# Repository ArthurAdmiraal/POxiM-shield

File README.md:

# POxiM-shield
 Prototyping Arduino shield for POxiM Pulse/Oxymeter

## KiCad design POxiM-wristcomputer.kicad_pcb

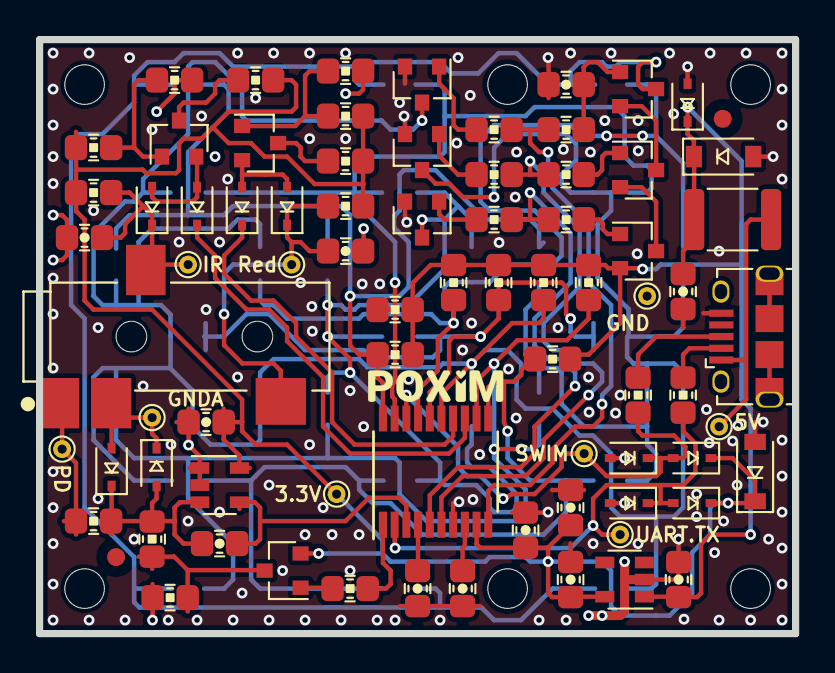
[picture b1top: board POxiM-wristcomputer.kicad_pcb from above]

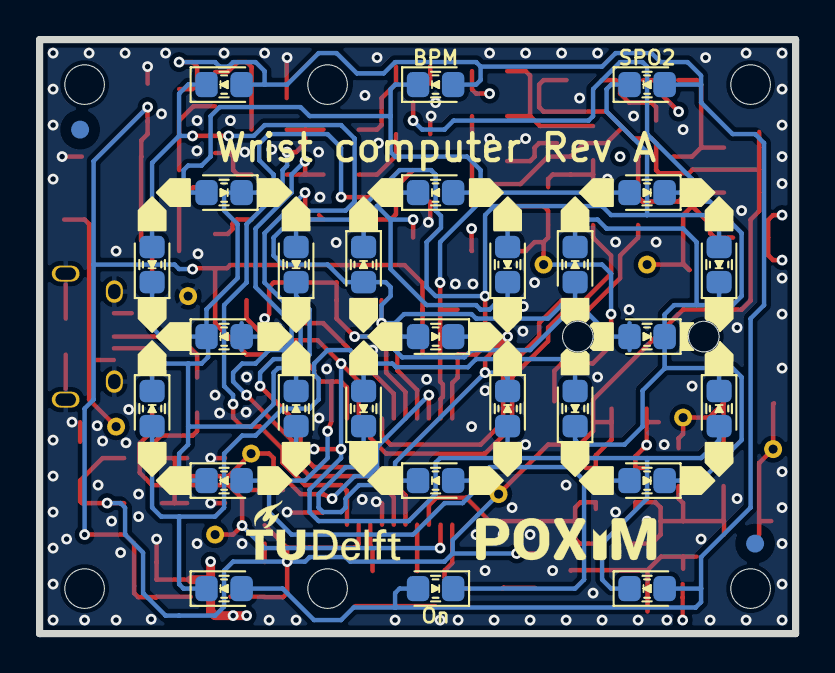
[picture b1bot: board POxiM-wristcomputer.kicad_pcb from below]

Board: 4 copper layers, 42.0 x 33.0 mm, 115 parts (35 on the bottom side), 50 nets.

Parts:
C1, C3, C7, C9, C11: 100nF; C_0805_2012Metric_0603_1608Metric
C2: 39pF; C_0805_2012Metric_0603_1608Metric
C4, C5, C6, C8, C12: 2.2µF; C_0805_2012Metric_0603_1608Metric
C10: 470nF; C_0805_2012Metric_0603_1608Metric
D1, D2, D3, D4, D5, D6, D35, D36, D37, D38, D39: Schottky; D_SOD-323
D7, D8, D9, D10, D11, D12, D13, D14, D15, D16, D17, D18, D19, D20, D21, D22, D23, D24, D25, D26, D27, D28, D29, D30, D31, D32, D33: LED; LED_0805_2012Metric_0603_1608Metric
D34: 6.8V; D_SOD-123
D40: 5.6V; D_SOD-123
F1: 500mA; R_1812_4532Metric
FID1, FID2, FID3, FID4: Fiducial; Fiducial_1mm_Mask2mm
H1, H2, H3, H4: MountingHole; MountingHole_2.2mm_M2
H5, H6: AlignmentHole; AlignmentHole_2.2mm_M2
J1: Power in; USB_Micro-B_Amphenol_10103594-0001LF_Horizontal
J2: To finger probe; CUI_SJ-43514-SMT
JP1: SWIM jumper; R_0805_2012Metric_0603_1608Metric
JP2: UART out jumper; R_0805_2012Metric_0603_1608Metric
NT1, NT2: Net-Tie_2; NetTie-2_SMD_Pad0.5mm
Q1, Q2, Q3: MMBT3904,215; SOT-23
Q4, Q5, Q6, Q7, Q8, Q9: PMBT3906,215; SOT-23
R1: 4.7MΩ; R_0805_2012Metric_0603_1608Metric
R2, R24, R25: 33kΩ; R_0805_2012Metric_0603_1608Metric
R3, R4: 100kΩ; R_0805_2012Metric_0603_1608Metric
R5, R6, R7, R8, R9, R10, R12: 560Ω; R_0805_2012Metric_0603_1608Metric
R11, R20: 2.2kΩ; R_0805_2012Metric_0603_1608Metric
R13, R14, R15, R16, R17, R18, R19, R21: 3.3kΩ; R_0805_2012Metric_0603_1608Metric
R22, R23: 68Ω; R_0805_2012Metric_0603_1608Metric
TP1: 5V in; TestPoint_THTPad_D1.0mm_Drill0.5mm
TP2: SWIM; TestPoint_THTPad_D1.0mm_Drill0.5mm
TP3: UART.TX; TestPoint_THTPad_D1.0mm_Drill0.5mm
TP4: GND; TestPoint_THTPad_D1.0mm_Drill0.5mm
TP5: PhotoDiode; TestPoint_THTPad_D1.0mm_Drill0.5mm
TP6: LED.Red; TestPoint_THTPad_D1.0mm_Drill0.5mm
TP7: GNDA; TestPoint_THTPad_D1.0mm_Drill0.5mm
TP8: LED.IR; TestPoint_THTPad_D1.0mm_Drill0.5mm
TP9: 3.3V; TestPoint_THTPad_D1.0mm_Drill0.5mm
U1: LM321; SOT-23-5
U2: STM8S003F3P; TSSOP-20_4.4x6.5mm_P0.65mm
U3: MIC5504-3.3YM5; SOT-23-5

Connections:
+3V3: C1.1, C5.1, C8.1, C9.1, D36.1, D38.1, D40.1, Q7.2, R11.2, R20.2, R22.2, R23.2, R24.2, R25.2, TP9.1, U1.5, U2.9, U3.5
+5V: C4.1, C11.1, D34.1, D35.1, F1.1, Q4.2, R5.1, R6.1, R7.1, R8.1, R9.1, R10.1, R12.1, U3.1
/Display/Common0: R14.2, R18.2, U2.6
/Display/Common1: R16.2, R17.2, U2.5
/Display/Common2: R15.2, R19.2, U2.10
/Display/Segment0: D7.2, D14.2, D21.1, D22.2, R12.2, U2.19
/Display/Segment1: D8.2, D15.2, D23.1, D24.2, R5.2, U2.17
/Display/Segment2: D9.2, D16.2, D25.1, D26.2, R6.2, U2.20
/Display/Segment3: D10.2, D17.2, D28.2, R7.2, U2.16
/Display/Segment4: D11.2, D18.2, D29.1, D30.2, R8.2, U2.15
/Display/Segment5: D12.2, D19.2, D31.1, D32.2, R9.2, U2.12
/Display/Segment6: D13.2, D20.2, D27.1, D33.2, R10.2, U2.11
/Microcontroller/ADC.feedback: R3.1, U2.1
/Microcontroller/ADC.input: C2.1, U1.4, U2.3
/Microcontroller/LED.IR: D2.1, U2.13
/Microcontroller/LED.Red: D1.1, U2.14
/Microcontroller/NRST: C7.1, U2.4
/Microcontroller/SWIM: D36.2, D37.1, JP1.2, TP2.1, U2.18
/Microcontroller/VCAP: C10.1, U2.8
/Signal conditioning/LEDOut.IR: C12.1, D4.1, J2.R1, R25.1, TP8.1
/Signal conditioning/LEDOut.Red: C6.1, D3.1, J2.T, R24.1, TP6.1
/Signal conditioning/PhotoDiode: J2.S, R2.2, TP5.1
/Signal conditioning/PhotoDiodeInternal: C2.2, D5.2, D6.1, R1.1, R2.1, U1.3
/USB interface/5V_input: F1.2, J1.1, TP1.1
/USB interface/Data+: J1.3, JP1.1
/USB interface/Data-: J1.2, JP2.1
/USB interface/DataTX: D38.2, D39.1, JP2.2, TP3.1, U2.2
GND: C3.2, C4.2, C5.2, C7.2, C8.2, C9.2, C10.2, C11.2, D34.2, D35.2, D37.2, D39.2, D40.2, J1.5, J1.6, NT1.1, NT2.1, Q1.2, Q2.2, Q3.2, TP4.1, U2.7, U3.2
GNDA: C6.2, C12.2, D5.1, D6.2, J2.R2, NT2.2, R13.1, R21.1, TP7.1
GNDREF: C1.2, NT1.2, R4.2, U1.1, U1.2
unnamed: C3.1, Q6.1, R19.1
unnamed: D1.2, D3.2, Q8.2
unnamed: D2.2, D4.2, Q9.2
unnamed: D7.1, D8.1, D9.1, D10.1, D11.1, D12.1, D13.1, Q1.3
unnamed: D14.1, D15.1, D16.1, D17.1, D18.1, D19.1, D20.1, Q3.3
unnamed: D21.2, D23.2, D25.2, D27.2, D29.2, D31.2, Q6.3
unnamed: D22.1, D24.1, D26.1, D28.1, D30.1, D32.1, D33.1, Q2.3
unnamed: Q1.1, R14.1
unnamed: Q2.1, R15.1
unnamed: Q3.1, R16.1
unnamed: Q4.1, R17.1
unnamed: Q4.3, Q5.2
unnamed: Q5.1, R18.1
unnamed: Q5.3, Q6.2
unnamed: Q7.1, R3.2
unnamed: Q7.3, R1.2, R4.1
unnamed: Q8.1, R11.1, R13.2
unnamed: Q8.3, R22.1
unnamed: Q9.1, R20.1, R21.2
unnamed: Q9.3, R23.1

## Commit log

2020-05-06 Create some example circuits
2020-05-07 Put design options in separate sheets
2020-05-10 Modify delta sigma for noise shaping with ADC, set analysis goals and analyse up to aliasing
2020-05-13 Initial block diagram, restructing to fit hierarchy
2020-05-13 NB: this shit is not finished
2020-05-13 schematic donish
2020-05-13 Add design note about debugger, remove superfluous files
2020-05-13 lib update
2020-05-13 begone
2020-05-14 looks real
2020-05-14 Start analysis on ADC nonlinearity
2020-05-14 big chungus
2020-05-14 Draw segments on user layer
2020-05-14 reduce digit spacing and export step
2020-05-15 Refactor based on feedback from Daniel
2020-05-15 Export mechanicacal files
2020-05-15 Finish display tester board Rev A
2020-05-16 Move around mechanical files
2020-05-17 Start documenting signal chain
2020-05-18 Finish works-as prototype design
2020-05-23 Finalise works-like prototype
2020-05-28 Add BOM
2020-05-28 Finish display tester board rev B
2020-05-28 Prepare and export schematic
2020-05-28 Correct render spellign mistake
2020-06-10 Start new LED drive method, some cleanup
2020-06-11 Finish signal conditioning cleanup, start reworking display
2020-06-11 Add diagram linking shorting locations to segments
2020-06-13 Update libraries
2020-06-15 Cleanup most of schematic
2020-07-01 Start reworking sing supply ripple issues.
2020-07-02 Initial PCB layout
2020-07-05 Finalise wrist computer rev A
2020-07-05 Cosmetic silkscreen changes, cleanup old files
2020-07-07 Update BOM
2020-07-16 Finish first schematic version
2020-09-07 Add supporting simulations, export BOM
